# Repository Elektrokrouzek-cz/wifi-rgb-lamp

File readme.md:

# Wifi RGB LED Lamp
This is the construction of Wifi controlled RGB LED lamp. It is based on ESP32-C3 super mini 
module and WS2812B LED strip and WLED project.

PCB is 2-layer and was designed using KiCad 10. Fabrication output for JLCPCB is in 
gerber folder.

**Happy soldering!**

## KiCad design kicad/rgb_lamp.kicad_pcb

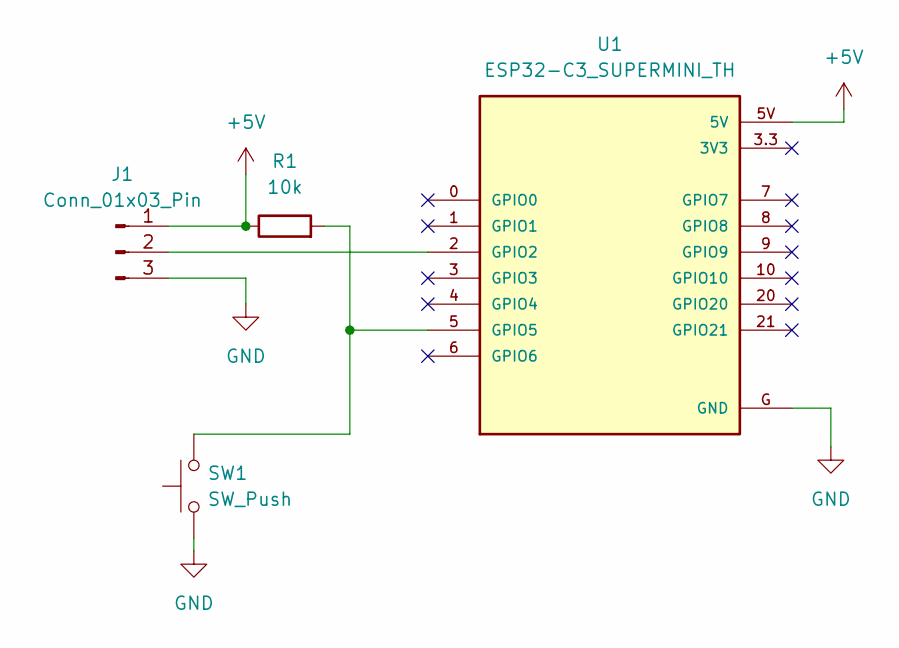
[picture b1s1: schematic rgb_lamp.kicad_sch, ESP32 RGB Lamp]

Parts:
J1: Conn_01x03_Pin; PinHeader_1x03_P2.54mm_Vertical
R1: 10k; R_1206_3216Metric_Pad1.30x1.75mm_HandSolder
SW1: SW_Push; SW_Tactile_SPST_Angled_PTS645Vx83-2LFS
U1: ESP32-C3_SUPERMINI_TH; MODULE_ESP32-C3_SUPERMINI

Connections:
+5V: J1.1, R1.1, U1.5V
GND: J1.3, SW1.1, U1.G (GND)
unnamed: J1.2, U1.2 (GPIO2)
unnamed: R1.2, SW1.2, U1.5 (GPIO5)

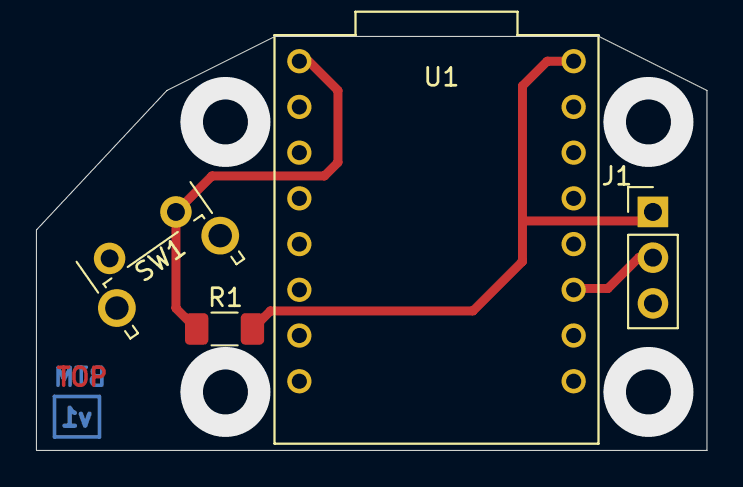
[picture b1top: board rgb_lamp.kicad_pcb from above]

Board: 2 copper layers, 37.2 x 23.0 mm, 4 parts (0 on the bottom side), 4 nets.
